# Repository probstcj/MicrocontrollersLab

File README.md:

# File System

Created for future reference. In each folder, there are 3 sub folders:
- Lab Documents
    - Contains all lab documents that are given by Dr. York
- Project
    - Contains entire project and workspace for PSoC Creator
- Report
    - Contains all necessary information for the report, will be given in both .docx, .odt, and .pdf format.
- Possible Issues
    - Known issues or possible issues for the project
- Notes
    - Notes for the project, helps for the small quiz he gives us during the demo.

# For Future Reference

Eventually, all labs will be named accordingly, but don't want to jump ahead. GIT should auto update those names accordingly without many issues.

# Before you PUSH to the Repository

Make sure to pull any updated files up to your local repository before pushing content to the repository.

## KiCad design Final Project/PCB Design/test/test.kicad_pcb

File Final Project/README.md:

# Automatic pet feeder

Inspiration: https://www.thingiverse.com/thing:4815584

## PSoC Creator Steps

### Here are the steps we need to take in order to get this project working.

1) Start printing stuff on I2C LCD
2) Get encoder interrupt working
3) Get button interrupt working
4) Settings for LCD
- If nothing, show the following per line:
    - Time and Date(will be set by RTC)
    - "Time of next feed:"
    - Time and Date of next feed
- If button is pressed, enter settings
    - Cycle through settings to show when encoder turns clockwise or counter-clockwise:
        - Set clock time
        - Set feed time(s)
        - Set amount of food/feed
        - Turn on/off Tone
        - Turn on/off Lights
- Per setting:
    - Set clock time:
        - Allow user to change RTC time
        - Use encoder to change hour, press button
        - Use encoder to change minute, press button
    - Set feed time(s)
        - First prompt for amount of times, use encoder to cyle through numbers up to 10 per day (if they try anymore, call their cat fat)
        - Once confirmed, cycle through amount, change hour and minute, same as clock time.
        - Set RTC to interrupt at these times.
    - Set amount of food/feed
        - Use horizontal bar, starting from zero
        - Per encoder turn, turn motor for testing
        - Move horizontal bar over
        - Once button is pressed, set number of steps for motor.
    - Turn on/off Tone
        - Either turn on or off the speakers when feed time
    - Turn on/off Lights
        - Either turn on or off the lights when feed time
5) Get RTC working
    - Needs to interrupt on a specific time
    - Needs to have correct real world time.
    - Do we need COT_IN?
    - Look in datasheets
6) On RTC interrupt
    - Turn motor specific amount of steps
    - Turn on speakers, if wanted
    - Turn on lights, if wanted
7) Setup UART?

# 5) Get web app working??

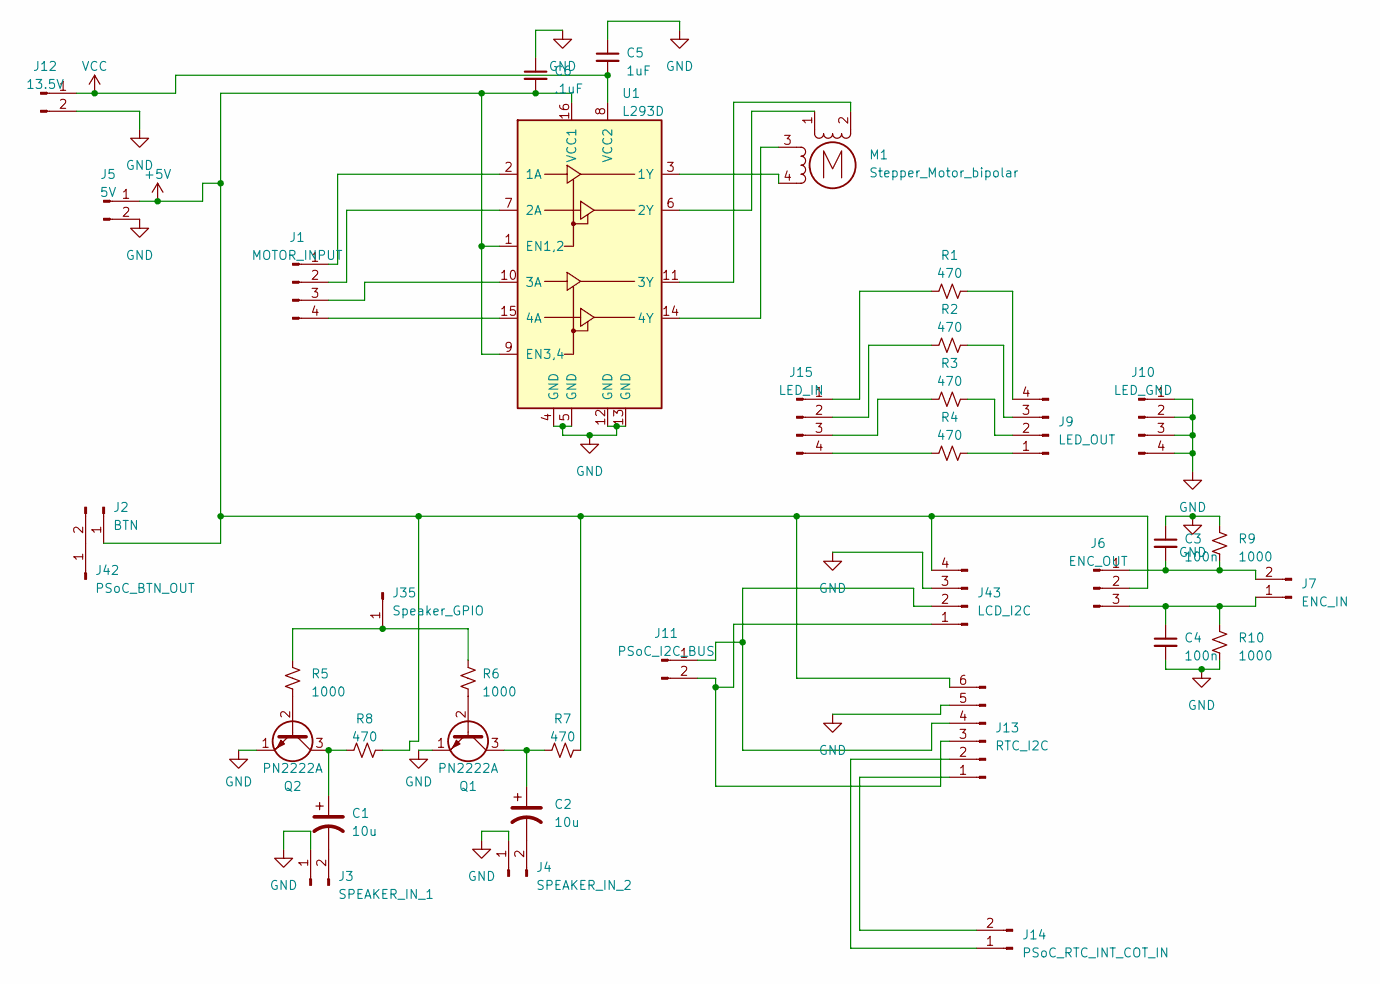
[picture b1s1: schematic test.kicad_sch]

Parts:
C1, C2: 10u; CP_Radial_D10.0mm_P7.50mm
C3, C4: 100n; C_Disc_D7.5mm_W5.0mm_P5.00mm
C5: 1uF; C_Disc_D8.0mm_W5.0mm_P5.00mm
C6: .1uF; C_Disc_D8.0mm_W5.0mm_P5.00mm
J1: MOTOR_INPUT; PinSocket_1x04_P2.54mm_Vertical
J2: BTN; PinHeader_1x02_P2.54mm_Vertical
J3: SPEAKER_IN_1; PinHeader_1x02_P2.54mm_Vertical
J4: SPEAKER_IN_2; PinHeader_1x02_P2.54mm_Vertical
J5: 5V; PinHeader_1x02_P2.54mm_Vertical
J6: ENC_OUT; PinHeader_1x03_P2.54mm_Vertical
J7: ENC_IN; PinHeader_1x02_P2.54mm_Vertical
J9: LED_OUT; PinSocket_1x04_P2.54mm_Vertical
J10: LED_GND; PinSocket_1x04_P2.54mm_Vertical
J11: PSoC_I2C_BUS; PinHeader_1x02_P2.54mm_Vertical
J12: 13.5V; PinHeader_1x02_P2.54mm_Vertical
J13: RTC_I2C; PinHeader_1x06_P2.54mm_Vertical
J14: PSoC_RTC_INT_COT_IN; PinHeader_1x02_P2.54mm_Vertical
J15: LED_IN; PinHeader_1x04_P2.54mm_Vertical
J35: Speaker_GPIO; PinHeader_1x01_P2.54mm_Vertical
J42: PSoC_BTN_OUT; PinHeader_1x01_P2.54mm_Vertical
J43: LCD_I2C; PinSocket_1x04_P2.54mm_Vertical
M1: Stepper_Motor_bipolar; PinSocket_1x04_P2.54mm_Vertical
Q1, Q2: PN2222A; PinHeader_1x03_P2.54mm_Vertical
R1, R2, R3, R4, R7, R8: 470; R_Axial_DIN0411_L9.9mm_D3.6mm_P12.70mm_Horizontal
R5, R6, R9, R10: 1000; R_Axial_DIN0411_L9.9mm_D3.6mm_P12.70mm_Horizontal
U1: L293D; DIP-16_W7.62mm

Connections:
+5V: C6.2, J2.1, J5.1, J6.2, J13.6, J43.4, R7.2, R8.2, U1.1 (EN1,2), U1.9 (EN3,4), U1.16 (VCC1)
GND: C3.1, C4.2, C5.1, C6.1, J3.1, J4.1, J5.2, J10.1, J10.2, J10.3, J10.4, J12.2, J13.5, J43.3, Q1.1 (E), Q2.1 (E), R9.2, R10.1, U1.4 (GND), U1.5 (GND), U1.12 (GND), U1.13 (GND)
unnamed: J1.1, U1.2 (1A)
unnamed: J1.2, U1.7 (2A)
unnamed: J1.3, U1.10 (3A)
unnamed: J1.4, U1.15 (4A)
unnamed: J2.2, J42.1
unnamed: C1.2, J3.2
unnamed: C2.2, J4.2
unnamed: C3.2, J6.1, J7.2, R9.1
unnamed: C4.1, J6.3, J7.1, R10.2
unnamed: J9.1, R4.2
unnamed: J9.2, R3.2
unnamed: J9.3, R2.2
unnamed: J9.4, R1.2
unnamed: J11.1, J13.4, J43.2
unnamed: J11.2, J13.3, J43.1
unnamed: J13.1, J14.2
unnamed: J13.2, J14.1
unnamed: J15.1, R1.1
unnamed: J15.2, R2.1
unnamed: J15.3, R3.1
unnamed: J15.4, R4.1
unnamed: J35.1, R5.1, R6.1
unnamed: M1.2 (-), U1.11 (3Y)
unnamed: Q1.2 (B), R6.2
unnamed: C2.1, Q1.3 (C), R7.1
unnamed: Q2.2 (B), R5.2
unnamed: C1.1, Q2.3 (C), R8.1
unnamed: M1.4, U1.3 (1Y)
unnamed: M1.1, U1.6 (2Y)
unnamed: M1.3, U1.14 (4Y)
VCC: C5.2, J12.1, U1.8 (VCC2)

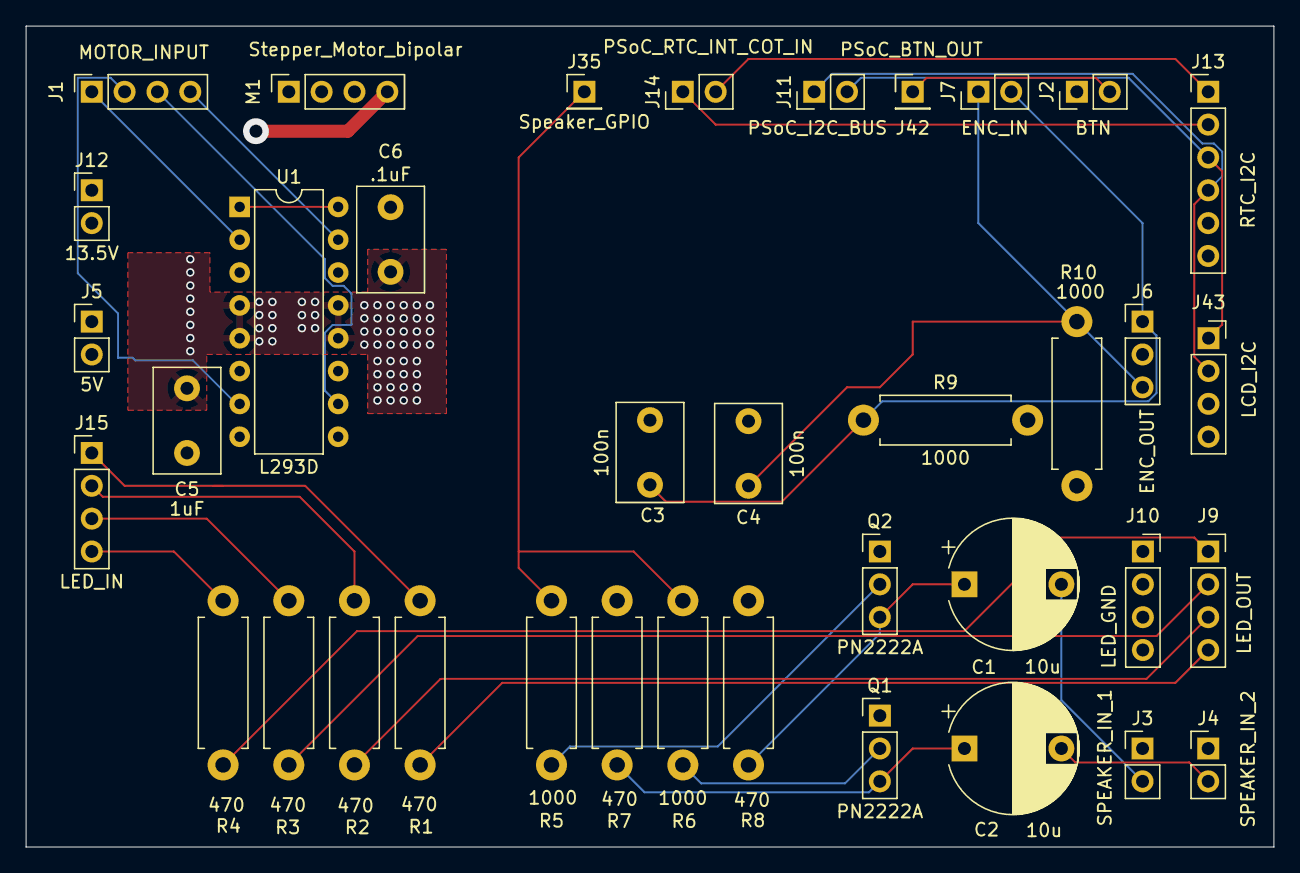
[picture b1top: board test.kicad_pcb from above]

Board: 4 copper layers, 96.5 x 63.5 mm, 37 parts (0 on the bottom side), 33 nets.

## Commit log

2023-01-11 Added file hierarchy and files
2023-01-11 Edit README.md
2023-01-11 Test rename
2023-01-11 Undo test
2023-01-13 Add Lab 00 to repo
2023-01-13 Added Lab 01 documents
2023-01-13 Added blank project for Lab 01
2023-01-17 Edited file design
2023-01-17 Change drive mode
2023-01-17 Example
2023-01-17 Example 2
2023-01-17 Added code for Lab 01
2023-01-18 Final commit for lab, done
2023-01-18 Add final project files
2023-01-19 Cleaned up code
2023-01-22 Added lab report
2023-01-22 Renamed lab report
2023-01-26 Added lab documents
2023-01-26 Added project
2023-01-27 Add zip
2023-01-28 Added back the removed files from project 1
2023-01-29 Add final project, hopefully finished
2023-01-29 Add project
2023-01-31 Reorganized project folders
2023-01-31 Added York's fix
2023-02-01 Added comments to all code
2023-02-02 Added lab 03
2023-02-02 Added changes to lab 03
2023-02-04 Added
2023-02-04 Sounds working at different frequencies
2023-02-05 Simon game finished
2023-02-05 Fixed repo
2023-02-06 Added report
2023-02-07 Added project 2
2023-02-07 Added project 3
2023-02-09 Added lab 4
2023-02-09 Added lab doc
2023-02-09 Added comments
2023-02-10 Added final project
2023-02-10 Added changes
2023-02-11 Error on folder name
2023-02-14 Finalized lab 4
2023-02-14 Final touches
2023-02-15 Added some bit level hacks
2023-02-15 Reversed
2023-02-15 Added dimensions
2023-02-15 Changed md
2023-02-15 Changed
2023-02-17 Removed odt
2023-02-23 Added lab 5
2023-02-23 Lab5 configuration
2023-03-10 Added 3d models and lab 5
2023-03-12 3D model
2023-03-12 edit lab 5
2023-03-15 Lab 5
2023-03-15 Finished lab 5
2023-03-15 Added comments to lab 5
2023-03-18 added pcb
2023-03-18 Edited pcb
2023-03-19 final 3D model design and PCB design
2023-03-20 add lab 6
2023-03-21 final pcb design?
2023-03-28 added lab 6
2023-03-28 added lab 5 report
2023-03-29 added 3d models
2023-03-29 added lab 3 again
2023-03-29 chose pins for final project
2023-03-29 added final project docs
2023-03-30 finalized lab 6
2023-04-01 final stuff
2023-04-03 added project proposal
2023-04-04 add lab 7
2023-04-04 added lab files
2023-04-04 lab 7 stuff
2023-04-06 added lab 6 comments
2023-04-08 added stuff
2023-04-09 added lab 7 comments
2023-04-10 added stuff for final
2023-04-11 final project update
2023-04-13 added lab 8
2023-04-13 finished lab 8
2023-04-19 added stuff for final project
2023-04-19 added reports
2023-04-22 added final stuff
2023-04-23 edit 3d model
2023-04-25 final project stuff
2023-04-26 added auger.stl
2023-04-30 added final
